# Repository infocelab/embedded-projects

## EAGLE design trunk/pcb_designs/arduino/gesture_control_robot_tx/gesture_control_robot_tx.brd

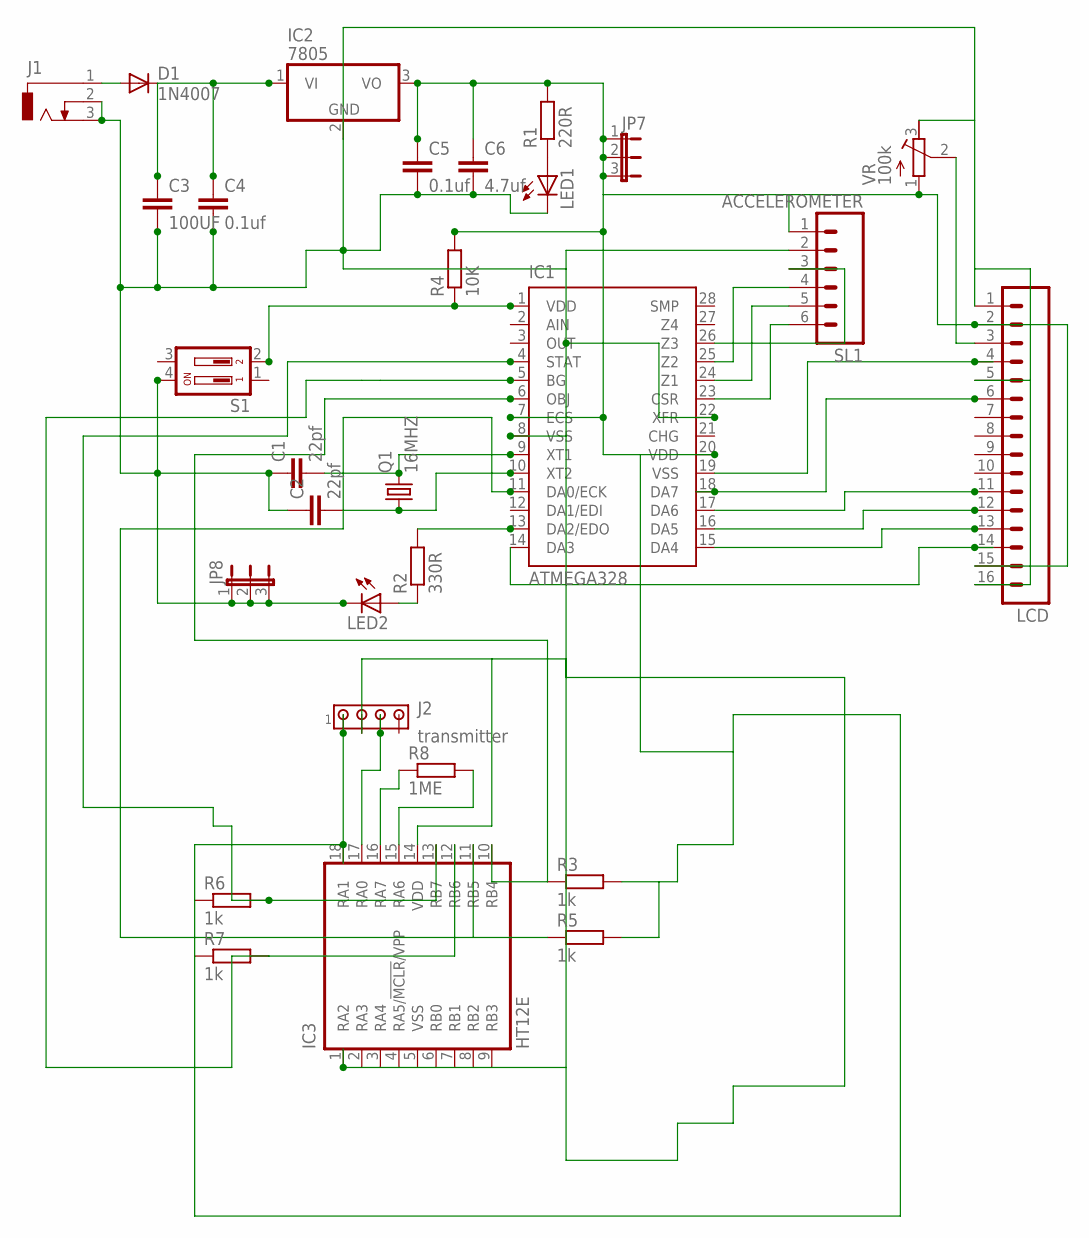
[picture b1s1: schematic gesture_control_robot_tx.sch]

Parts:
C1, C2: 22pf; C2.5-2
C3: 100UF; C2.5-2
C4, C5: 0.1uf; C2.5-2
C6: 4.7uf; C2.5-2
D1: 1N4007; DO41-10
IC1: ATMEGA328; DIL28-3
IC2: 7805; TO220V
IC3: HT12E; DIL18
J1: DCJ0303
J2: transmitter; 10X04MTA
JP7, JP8: JP2E; JP2
LCD: M16; 16P
LED1, LED2: LED3MM
Q1: 16MHZ; HC49/S
R1: 220R; 0207/10
R2: 330R; 0207/10
R3, R5, R6, R7: 1k; 0204/7
R4: 10K; 0207/10
R8: 1ME; 0204/7
S1: DP02; DP-02
SL1: ACCELEROMETER; 06P
VR: 100k; RTRIM64P

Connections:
unnamed: C1.2, IC1.9 (XT1), Q1.2
unnamed: C2.2, IC1.10 (XT2), Q1.1
unnamed: D1.A, J1.1
unnamed: C5.1, C6.1, IC1.7 (ECS), IC1.20 (VDD), IC2.3 (VO), IC3.18 (RA1), J2.1, JP7.1, JP7.2, JP7.3, LCD.2, LCD.15, R1.2, R3.2, R4.2, R5.2, R6.1, R7.1, SL1.1, VR.1 (E)
unnamed: C1.1, C2.1, C3.2, C4.2, C5.2, C6.2, IC1.8 (VSS), IC1.22 (XFR), IC2.2 (GND), IC3.1 (RA2), IC3.2 (RA3), IC3.3 (RA4), IC3.4 (RA5/!MCLR!/VPP), IC3.5 (VSS), IC3.6 (RB0), IC3.7 (RB1), IC3.8 (RB2), IC3.9 (RB3), IC3.14 (VDD), J1.2, J1.3, J2.2, JP8.1, JP8.2, JP8.3, LCD.1, LCD.5, LCD.16, LED1.K (C), LED2.K (C), S1.4, SL1.2, VR.3 (A)
unnamed: LED1.A, R1.1
unnamed: C3.1, C4.1, D1.C, IC2.1 (VI)
unnamed: IC1.23 (CSR), SL1.6
unnamed: IC1.24 (Z1), SL1.5
unnamed: IC1.25 (Z2), SL1.4
unnamed: IC1.26 (Z3), SL1.3
unnamed: IC1.13 (DA2/EDO), R2.2
unnamed: LCD.3, VR.2 (S)
unnamed: IC1.19 (VSS), LCD.4
unnamed: IC1.18 (DA7), LCD.6
unnamed: IC1.17 (DA6), LCD.11
unnamed: IC1.16 (DA5), LCD.12
unnamed: IC1.15 (DA4), LCD.13
unnamed: IC1.14 (DA3), LCD.14
unnamed: IC1.6 (OBJ), IC3.10 (RB4), R3.1
unnamed: IC1.1 (VDD), R4.1, S1.2
unnamed: LED2.A, R2.1
unnamed: IC1.11 (DA0/ECK), IC3.11 (RB5), R5.1
unnamed: IC1.5 (BG), IC3.12 (RB6), R7.2
unnamed: IC1.4 (STAT), IC3.13 (RB7), R6.2
unnamed: IC3.16 (RA7), R8.1
unnamed: IC3.15 (RA6), R8.2
unnamed: IC3.17 (RA0), J2.3

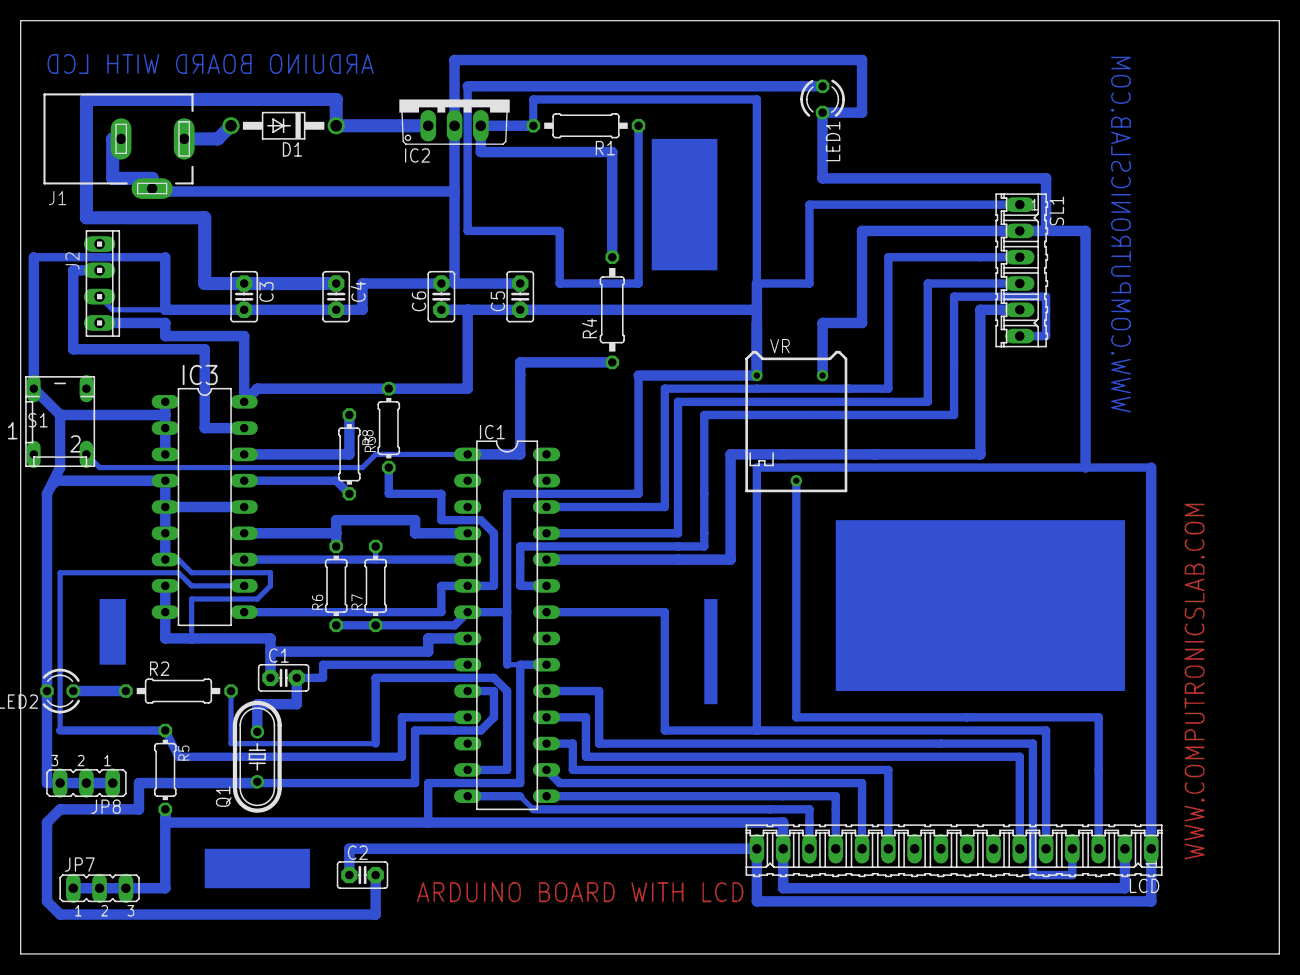
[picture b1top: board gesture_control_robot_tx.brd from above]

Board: 2 copper layers, 121.6 x 90.2 mm, 29 parts (0 on the bottom side), 28 nets.

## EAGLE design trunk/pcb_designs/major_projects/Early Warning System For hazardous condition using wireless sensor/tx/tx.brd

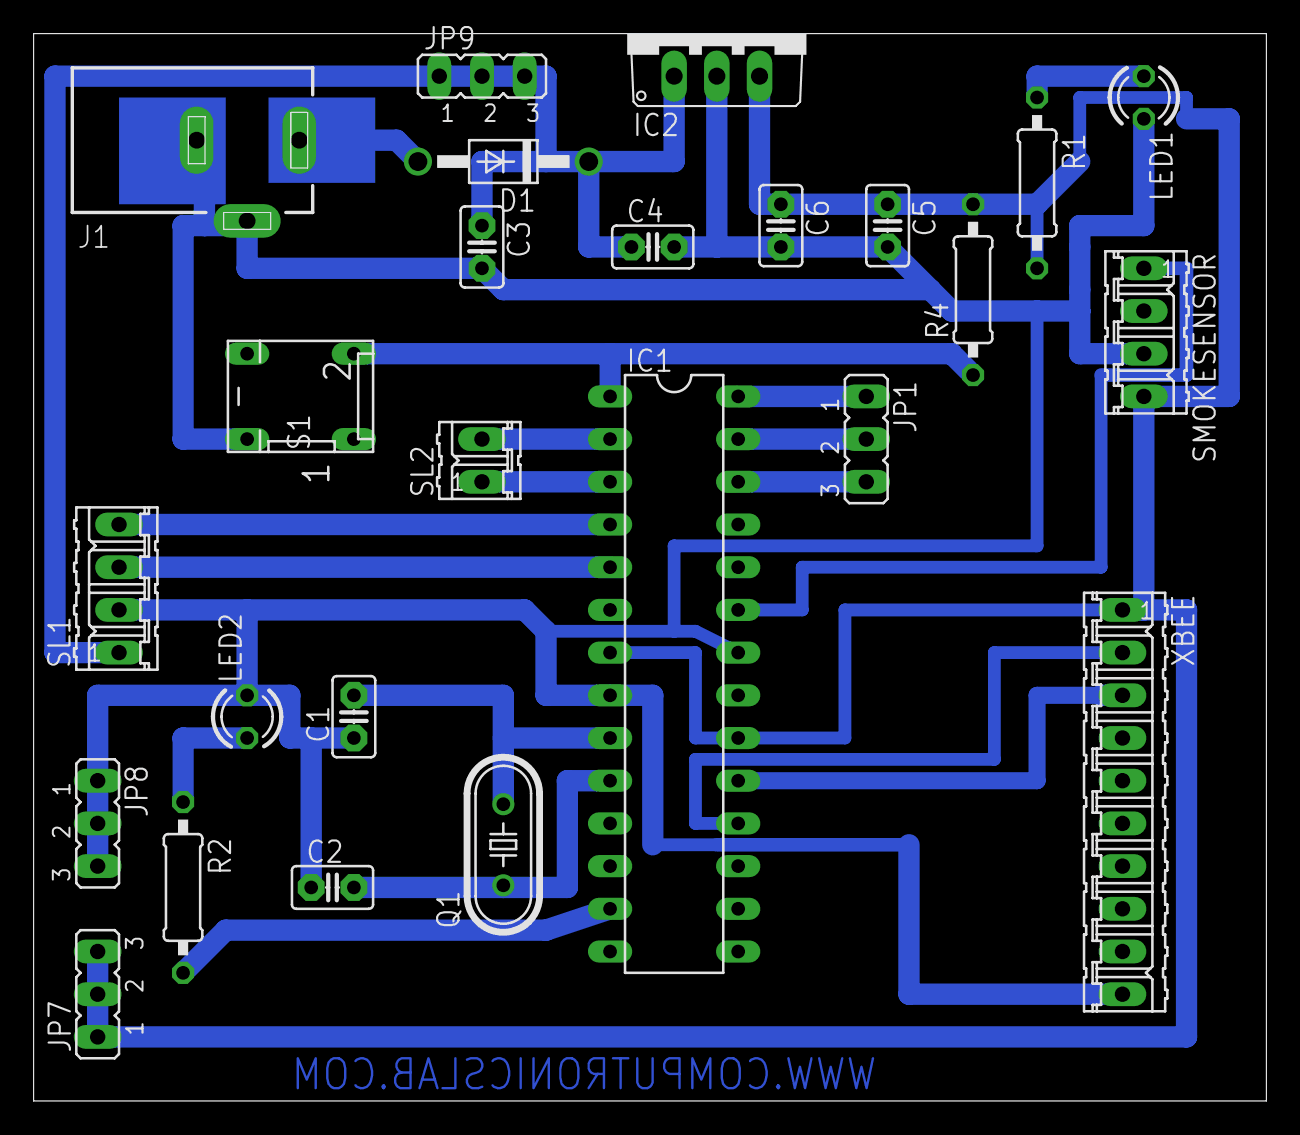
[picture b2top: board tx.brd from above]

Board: 2 copper layers, 73.3 x 63.5 mm, 25 parts (0 on the bottom side), 20 nets.

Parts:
C1, C2: 22pf; C2.5-2
C3: 100UF; C2.5-2
C4, C5: 0.1uf; C2.5-2
C6: 4.7uf; C2.5-2
D1: 1N4007; DO41-10
IC1: ATMEGA328; DIL28-3
IC2: 7805; TO220V
J1: DCJ0303
JP1, JP7, JP8, JP9: JP2
LED1, LED2: LED3MM
Q1: 16MHZ; HC49/S
R1: 220R; 0207/10
R2: 330R; 0207/10
R4: 10K; 0207/10
S1: DP-02
SL1: GSM; 04P
SL2: 02P
SMOKESENSOR: 04P
XBEE: 10P

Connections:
unnamed: C1.2, IC1.9, Q1.2
unnamed: C2.2, IC1.10, Q1.1
unnamed: D1.A, J1.1
unnamed: C5.1, C6.1, IC1.7, IC1.20, IC2.3, JP7.1, JP7.2, JP7.3, R1.2, R4.2, SMOKESENSOR.4, XBEE.1
unnamed: C1.1, C2.1, C3.2, C4.2, C5.2, C6.2, IC1.8, IC1.22, IC2.2, J1.2, J1.3, JP8.1, JP8.2, JP8.3, LED1.K, LED2.K, S1.4, SL1.2, SMOKESENSOR.3, XBEE.10
unnamed: LED1.A, R1.1
unnamed: C3.1, C4.1, D1.C, IC2.1, JP9.1, JP9.2, JP9.3, SL1.1
unnamed: IC1.28, JP1.1
unnamed: IC1.27, JP1.2
unnamed: IC1.26, JP1.3
unnamed: IC1.18, XBEE.2
unnamed: IC1.19, XBEE.3
unnamed: IC1.23, SMOKESENSOR.1
unnamed: IC1.5, SL1.3
unnamed: IC1.2, SL2.2
unnamed: IC1.3, SL2.1
unnamed: IC1.4, SL1.4
unnamed: IC1.13, R2.2
unnamed: IC1.1, R4.1, S1.2
unnamed: LED2.A, R2.1

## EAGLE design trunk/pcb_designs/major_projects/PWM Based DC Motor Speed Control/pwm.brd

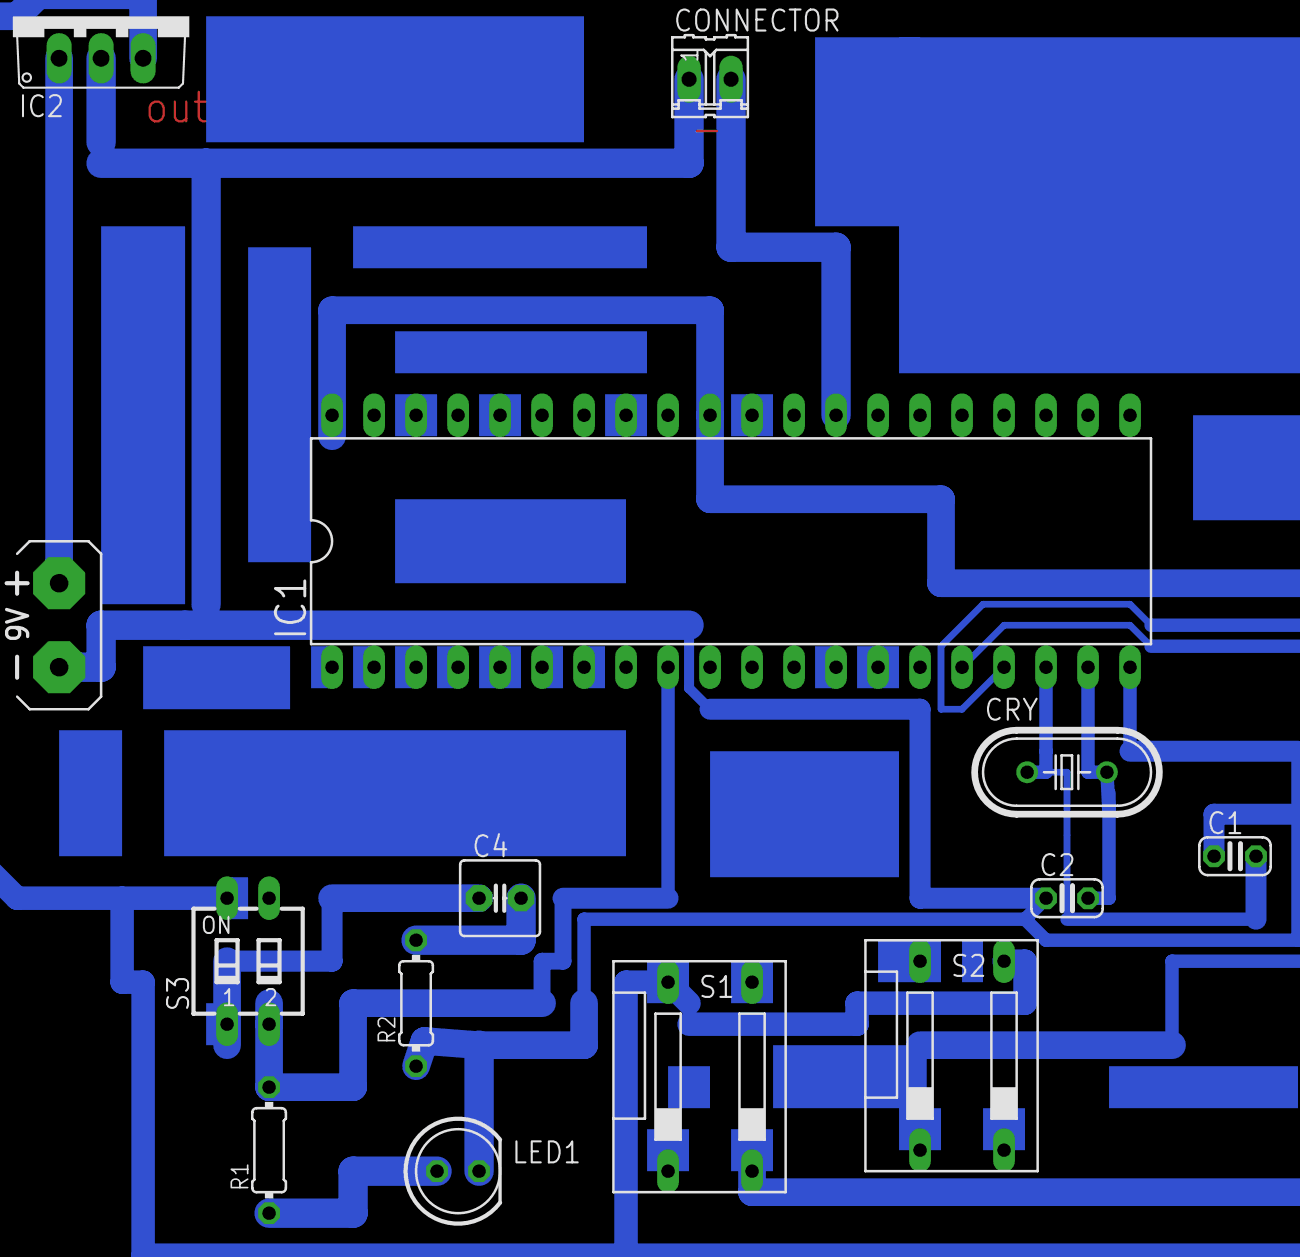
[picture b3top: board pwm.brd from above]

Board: 2 copper layers, 14 parts (0 on the bottom side), 13 nets.

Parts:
C1, C2: 33pf; C025-024X044
C4: 10uf; C2.5-5
CONNECTOR: 2 PIN; 02P
CRY: 11.0592 mhz; HC49U70
G1: AB9V
IC1: 8051; DIL40
IC2: 7805TV; TO220V
LED1: 5MM; LED5MM
R1: 220E; 0204/7
R2: 10K; 0204/7
S1, S2: PUSH SWITCH; DS-02
S3: PUSH SWITCH; SD4-02

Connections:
unnamed: C1.2, CRY.1, IC1.18
unnamed: C2.2, CRY.2, IC1.19
unnamed: IC1.17, S1.2
unnamed: G1.+, IC2.1
unnamed: C4.2, R2.2
unnamed: IC1.16, S2.1
unnamed: C4.1, S3.1
unnamed: C1.1, C2.1, CONNECTOR.1, G1.-, IC1.20, IC2.2, LED1.K, R2.1
unnamed: IC1.9, R1.2, S3.2
unnamed: LED1.A, R1.1
unnamed: CONNECTOR.2, IC1.28
unnamed: IC1.31, IC2.3, S1.4, S2.3, S3.4
VDD: IC1.11, IC1.32

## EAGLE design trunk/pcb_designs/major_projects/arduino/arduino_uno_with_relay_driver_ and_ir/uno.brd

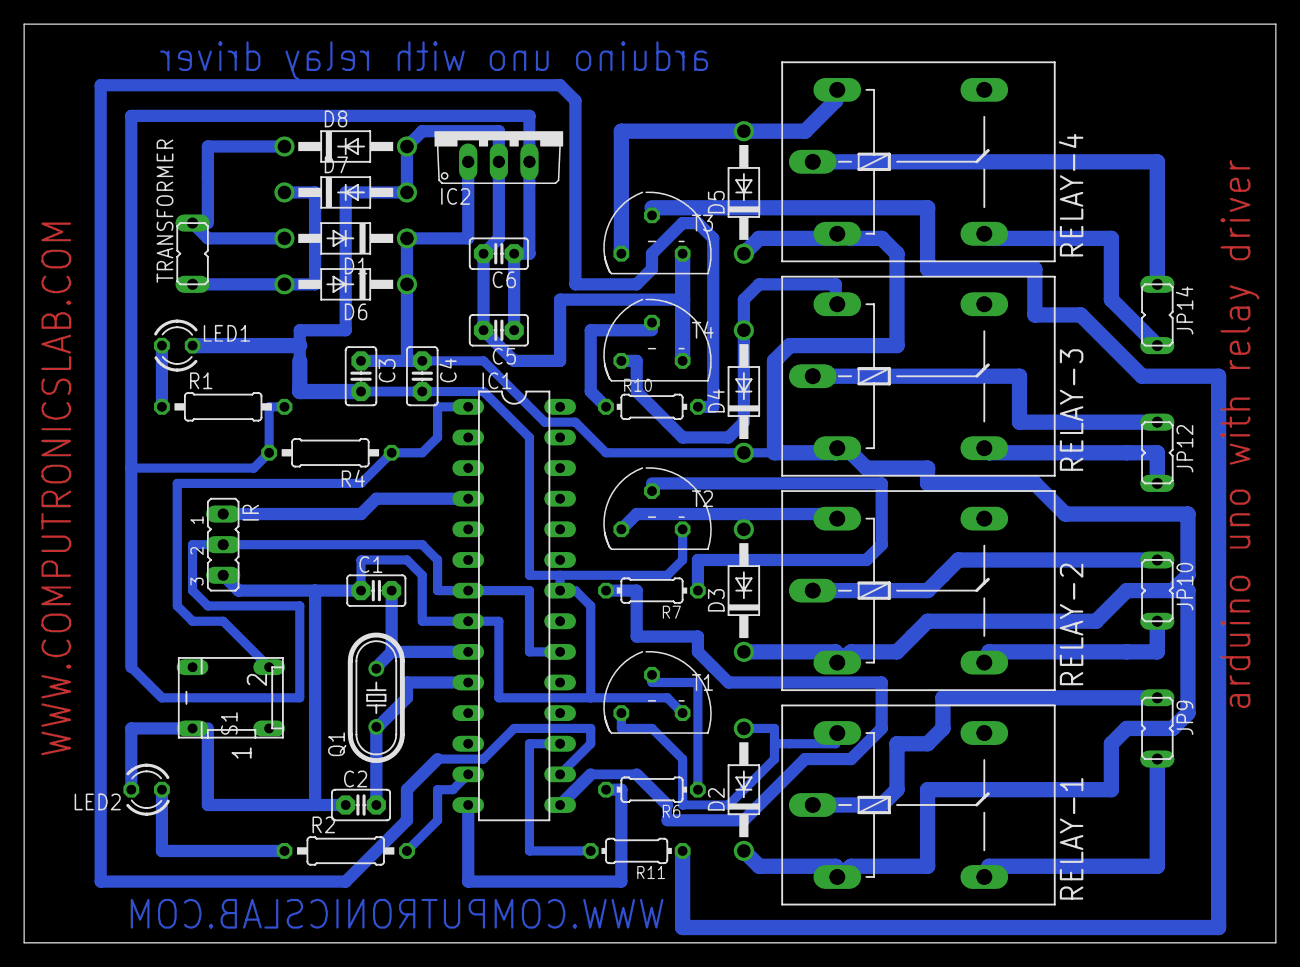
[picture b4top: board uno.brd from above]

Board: 2 copper layers, 103.8 x 76.2 mm, 41 parts (0 on the bottom side), 32 nets.

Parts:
C1, C2: 22pf; C2.5-2
C3: 470uF; C2.5-2
C4, C5: 0.1uf; C2.5-2
C6: 4.7uf; C2.5-2
D1, D2, D3, D4, D5, D6, D7, D8: 1N4007; DO41-10
IC1: ATMEGA328; DIL28-3
IC2: 7805; TO220V
IR: 3 pin; JP2
JP9, JP10, JP12, JP14: AC CONNECTOR; JP1
LED1, LED2: LED3MM
Q1: 12MHZ; HC49/S
R1: 220R; 0207/10
R2: 330R; 0207/10
R4: 10K; 0207/10
R6, R7, R10, R11: 5.6K; 0204/7
RELAY-1, RELAY-2, RELAY-3, RELAY-4: 12V; G5LE
S1: DP-02
T1, T2, T3, T4: BC547; TO92
TRANSFORMER: AC CONNECTOR; JP1

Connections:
unnamed: C1.2, IC1.9, Q1.2
unnamed: C2.2, IC1.10, Q1.1
unnamed: D6.A, D7.C, TRANSFORMER.1
unnamed: C5.1, C6.1, IC1.7, IC1.20, IC2.3, IR.2, R1.2, R4.2
unnamed: LED1.A, R1.1
unnamed: C3.1, C4.1, D1.C, D2.C, D3.C, D4.C, D5.C, D6.C, IC2.1, RELAY-1.1, RELAY-2.1, RELAY-3.1, RELAY-4.1
unnamed: IC1.4, IR.1
unnamed: D1.A, D8.C, TRANSFORMER.2
unnamed: IC1.13, R2.2
unnamed: C1.1, C2.1, C3.2, C4.2, C5.2, C6.2, D7.A, D8.A, IC1.8, IC1.22, IC2.2, IR.3, LED1.K, LED2.K, S1.4, T1.1, T2.1, T3.1, T4.1
unnamed: D2.A, RELAY-1.2, T1.3
unnamed: R7.1, T2.2
unnamed: R6.1, T1.2
unnamed: IC1.1, R4.1, S1.2
unnamed: LED2.A, R2.1
unnamed: JP9.2, RELAY-1.S
unnamed: JP9.1, RELAY-1.P
unnamed: JP10.2, RELAY-2.S
unnamed: JP10.1, RELAY-2.P
unnamed: IC1.14, R6.2
unnamed: D3.A, RELAY-2.2, T2.3
unnamed: D4.A, RELAY-3.2, T4.3
unnamed: R11.1, T3.2
unnamed: R10.1, T4.2
unnamed: JP12.2, RELAY-3.S
unnamed: JP12.1, RELAY-3.P
unnamed: JP14.2, RELAY-4.S
unnamed: JP14.1, RELAY-4.P
unnamed: IC1.16, R10.2
unnamed: IC1.17, R11.2
unnamed: D5.A, RELAY-4.2, T3.3
unnamed: IC1.15, R7.2

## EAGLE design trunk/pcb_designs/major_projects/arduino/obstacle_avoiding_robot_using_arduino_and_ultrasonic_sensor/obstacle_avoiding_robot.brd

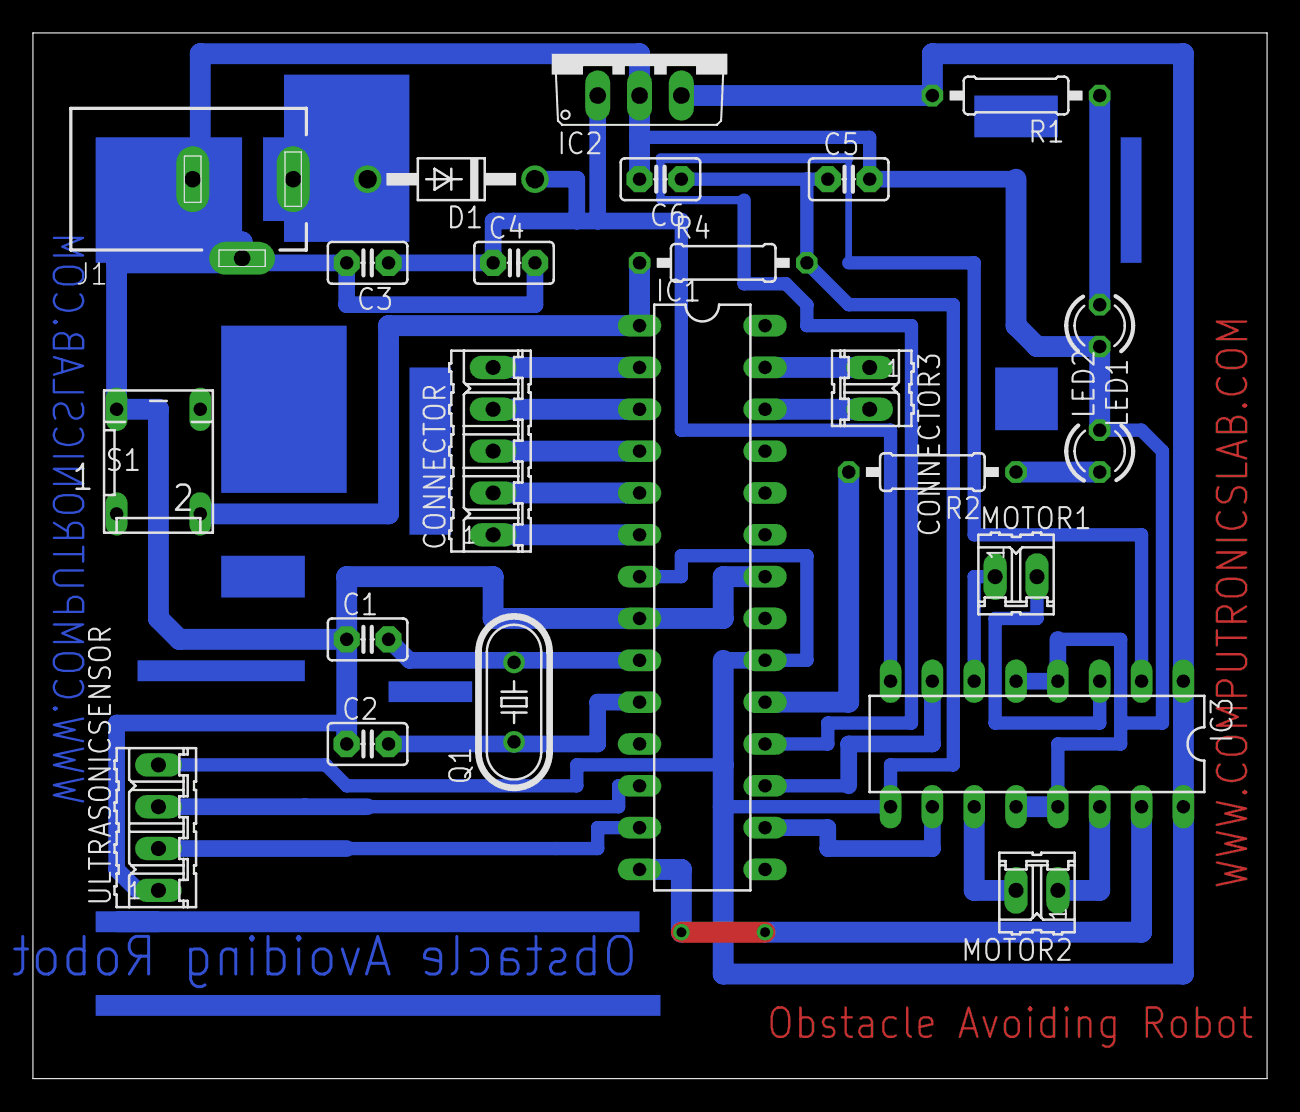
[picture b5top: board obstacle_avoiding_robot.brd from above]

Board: 2 copper layers, 74.9 x 63.5 mm, 23 parts (0 on the bottom side), 27 nets.

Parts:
C1, C2: 22pf; C2.5-2
C3: 470uF; C2.5-2
C4, C5: 0.1uf; C2.5-2
C6: 4.7uf; C2.5-2
CONNECTOR: 6 pin; 05P
CONNECTOR3: 02P
D1: 1N4007; DO41-10
IC1: ATMEGA328; DIL28-3
IC2: 7805; TO220V
IC3: L293D; DIL16
J1: DCJ0303
LED1, LED2: 3mm; LED3MM
MOTOR1, MOTOR2: 02P
Q1: 16MHZ; HC49/S
R1: 220R; 0207/10
R2: 330R; 0207/10
R4: 10K; 0207/10
S1: push switch; DP-02
ULTRASONICSENSOR: 4 pin; 04P

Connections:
unnamed: C1.2, IC1.9, Q1.2
unnamed: C2.2, IC1.10, Q1.1
unnamed: D1.A, J1.1
unnamed: C3.1, C4.1, D1.C, IC2.1, IC3.8
unnamed: C1.1, C2.1, C3.2, C4.2, C5.2, C6.2, IC1.8, IC1.22, IC2.2, IC3.4, IC3.5, IC3.12, IC3.13, J1.2, J1.3, LED1.K, LED2.K, S1.4, ULTRASONICSENSOR.1
unnamed: LED1.A, R1.1
unnamed: IC1.17, IC3.7
unnamed: CONNECTOR.1, IC1.6
unnamed: CONNECTOR.2, IC1.5
unnamed: CONNECTOR.3, IC1.4
unnamed: CONNECTOR.4, IC1.3
unnamed: CONNECTOR3.1, IC1.27
unnamed: CONNECTOR3.2, IC1.26
unnamed: CONNECTOR.5, IC1.2
unnamed: IC1.18, IC3.2
unnamed: IC1.14, IC3.15
unnamed: IC1.12, ULTRASONICSENSOR.3
unnamed: IC1.13, ULTRASONICSENSOR.2
unnamed: IC1.16, IC3.10
unnamed: IC3.14, MOTOR2.1
unnamed: IC1.19, R2.2
unnamed: IC3.11, MOTOR2.2
unnamed: IC1.1, R4.1, S1.2
unnamed: LED2.A, R2.1
unnamed: C5.1, C6.1, IC1.7, IC1.20, IC2.3, IC3.1, IC3.9, IC3.16, R1.2, R4.2, ULTRASONICSENSOR.4
unnamed: IC3.6, MOTOR1.1
unnamed: IC3.3, MOTOR1.2

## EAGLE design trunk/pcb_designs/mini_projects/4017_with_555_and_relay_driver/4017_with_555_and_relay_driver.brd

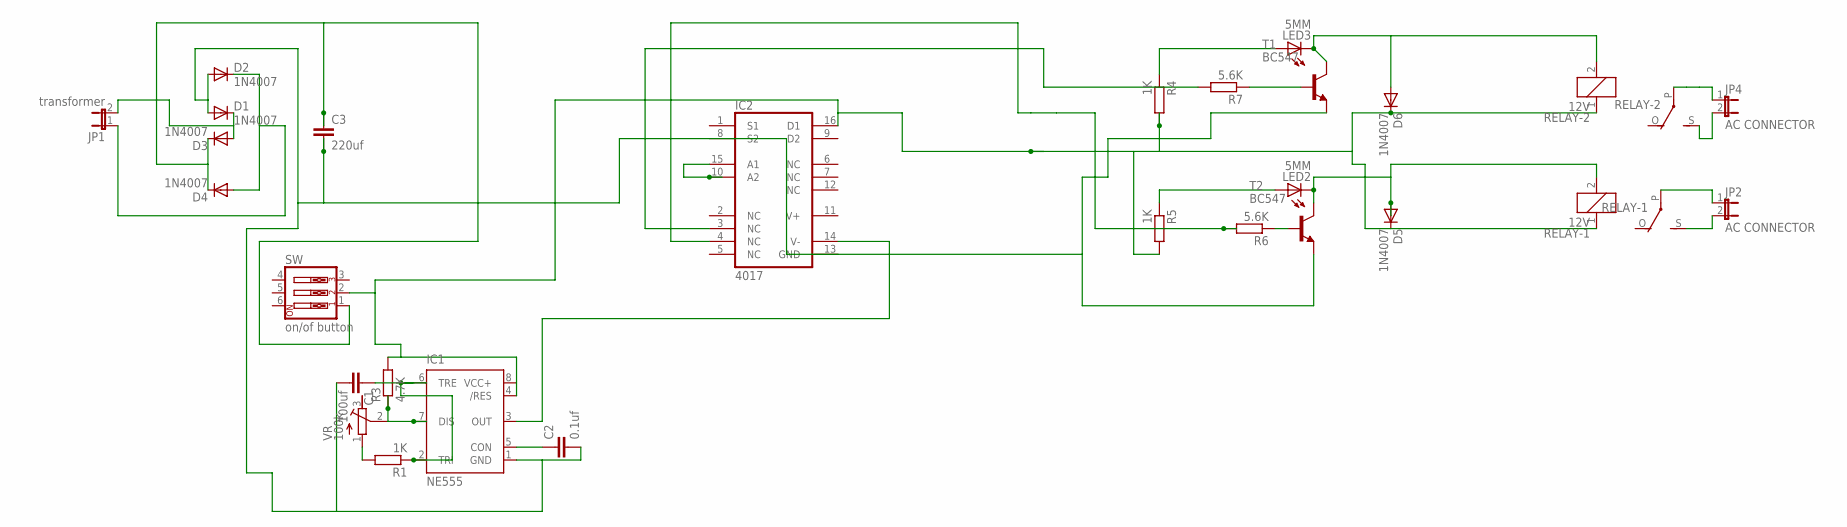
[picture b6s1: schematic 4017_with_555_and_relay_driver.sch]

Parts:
C1: 100uf; C025-050X050
C2: 0.1uf; C025-050X050
C3: 220uf; C5B7.2
D1, D2, D3, D4, D5, D6: 1N4007; DO41-10
IC1: NE555; DIL-08
IC2: 4017; DIL16
JP1: transformer; JP1
JP2, JP4: AC CONNECTOR; JP1
LED2, LED3: 5MM; LED5MM
R1, R4, R5: 1K; 0204/7
R3: 4.7K; 0204/7
R6, R7: 5.6K; 0204/7
RELAY-1, RELAY-2: 12V; G5LE
SW: on/of button; EDG-03
T1, T2: BC547; TO92
VR: 100k; RTRIM64P

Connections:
unnamed: C1.1, IC1.2 (TRI), IC1.6 (TRE), R1.1
unnamed: C2.1, IC1.5 (CON)
unnamed: IC1.7 (DIS), R3.1, VR.2 (S)
unnamed: IC1.3 (OUT), IC2.14 (V-)
unnamed: D5.C, D6.C, IC1.4 (/RES), IC1.8 (VCC+), IC2.16 (D1), R3.2, R4.2, R5.2, RELAY-1.1, RELAY-2.1, SW.2
unnamed: R1.2, VR.1 (E)
unnamed: IC2.10 (A2), IC2.15 (A1)
unnamed: C1.2, C2.2, C3.2, D1.A, D2.A, IC1.1 (GND), IC2.8 (S2), IC2.13 (GND), T1.1 (E), T2.1 (E)
unnamed: C3.1, D3.C, D4.C, SW.1
unnamed: D2.C, D4.A, JP1.1
unnamed: D1.C, D3.A, JP1.2
unnamed: D5.A, LED2.K (C), RELAY-1.2, T2.3 (C)
unnamed: R7.1, T1.2 (B)
unnamed: R6.1, T2.2 (B)
unnamed: LED2.A, R5.1
unnamed: LED3.A, R4.1
unnamed: JP2.2, RELAY-1.S
unnamed: JP2.1, RELAY-1.P
unnamed: JP4.2, RELAY-2.S
unnamed: JP4.1, RELAY-2.P
unnamed: IC2.4 (NC), R6.2
unnamed: IC2.3 (NC), R7.2
unnamed: D6.A, LED3.K (C), RELAY-2.2, T1.3 (C)
V+: IC2.11 (V+)

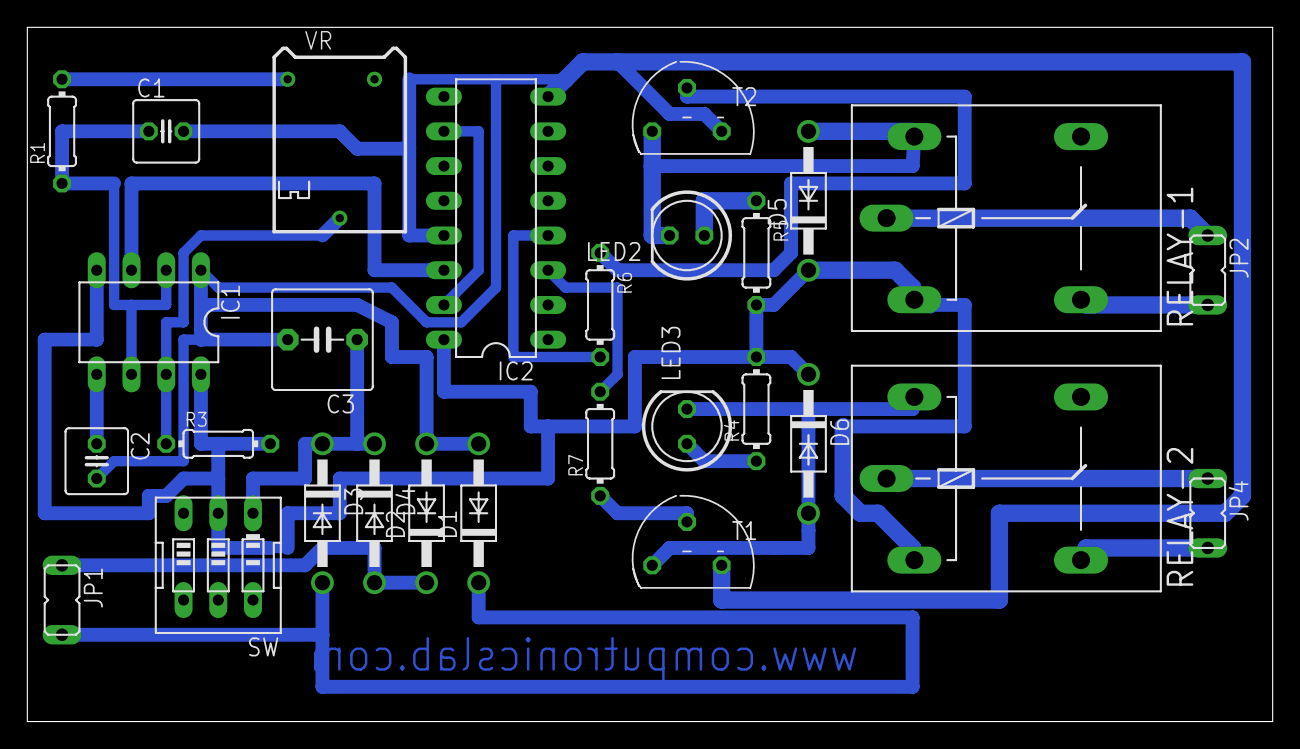
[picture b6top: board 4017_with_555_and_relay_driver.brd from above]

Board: 2 copper layers, 91.1 x 50.8 mm, 28 parts (0 on the bottom side), 23 nets.

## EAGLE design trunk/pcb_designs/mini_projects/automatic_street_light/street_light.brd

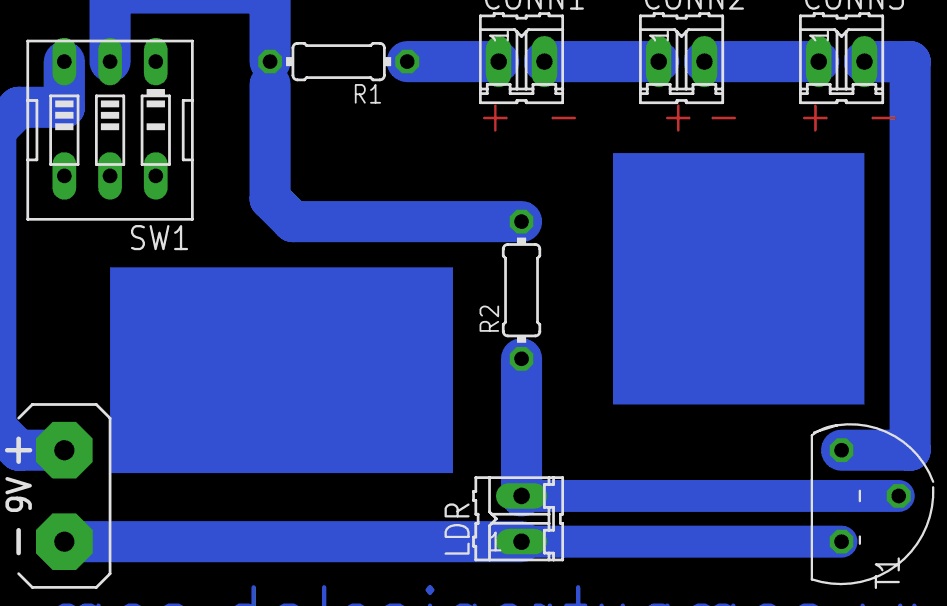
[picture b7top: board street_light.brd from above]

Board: 2 copper layers, 9 parts (0 on the bottom side), 8 nets.

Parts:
CONN1, CONN2, CONN3: 2 PIN; 02P
G1: AB9V
LDR: 02P
R1: 220E; 0204/7
R2: 100k; 0204/7
SW1: EDG-03
T1: BC547; TO92

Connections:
unnamed: CONN1.1, R1.1
unnamed: CONN1.2, CONN2.1
unnamed: CONN2.2, CONN3.1
unnamed: CONN3.2, T1.3
unnamed: G1.+, SW1.3
unnamed: R1.2, R2.2, SW1.2
unnamed: LDR.2, R2.1, T1.2
unnamed: G1.-, LDR.1, T1.1
